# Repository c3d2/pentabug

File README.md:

pentabug
========

**If you experience difficulties with your bug, please check the [troubleshooting documentation](https://github.com/c3d2/pentabug/blob/master/troubleshooting.md).**

The pentabug is a small microcontroller soldering project. It's especially suited for young hackers and beginners of all ages. Assembly requires no prior soldering skills and can be accomplished - with a little help for the tricky parts - by children old enough to savely hold a soldering iron (thats about 7 years and up).

At various events, e.g. [Datenspuren 2012 and 2013](http://datenspuren.de "Datenspuren 2012 and 2013"), Chaos Communication Congress 2012-2015, and many more, several hundred kits have been successfully assembled with just a handfull of bugs needing 'special treatment' for e.g. a controller mounted the wrong way. Have a look at our [slides in german](/c3d2/pentabug/raw/master/doc/201210_slides_datenspuren.pdf "slides form the Datenspuren 2012 talk") from the accompanying [presentation](http://www.datenspuren.de/2012/fahrplan/events/5074.de.html "pentabug talk announcement") or watch [this video](http://www.youtube.com/watch?v=HTBhXqNR6LY "Dresdner Piratencast Folge 14 - Datenspuren") of Frank and his sons beeing interviewed at our workshop table or the [NDR report](https://www.ndr.de/fernsehen/sendungen/hamburg_journal/Kleine-Hacker-am-Werk,hamj45298.html) covering the 32c3 Junghackertag.

A complete walktrough of the assembly process is given in ["Pentabug - The Movie"](http://www.c3d2.de/news/video-pentabug-bauen.html "Pentabug - The Movie"), courtesy of [C3D2 - Chaos Computer Club Dresden](http://c3d2.de "C3D2 - Chaos Computer Club Dresden"). It would be amazing if Scott Manley could do an english version ;-). I would even visit SF to make that happen. 

Img. 1: A completely assembled V2 PCB with extension boards.

Img. 2: A slightly advanced (but early) prototype version of the bug with a single layer pcb.

Img. 3: The top layer view of the Version 1.0 production board (two layer pcb).

Img. 4: Version 2.1 schematics ([high resolution image](https://github.com/c3d2/pentabug/raw/master/img/schematics_v2_1.png "high resolution image of schematics")).

[Bill of Materials for Version 1.0](https://github.com/c3d2/pentabug/blob/master/bom.md "bill of materials") - CAVE: This is outdated for the V2.0 and V2.1 versions.

Programming
===========

A quite comprehensive documentation in German for setting up the development toolchain is available at [RHOIO's Blog](https://rhoio.wordpress.com/2014/02/06/den-pentabug-programmieren/).

AVR GCC Toolchain
------------------

 * install binutils-avr, gcc-avr, avr-libc, avrdude
 <pre><code>sudo apt-get install binutils-avr gcc-avr avr-libc avrdude</code></pre>

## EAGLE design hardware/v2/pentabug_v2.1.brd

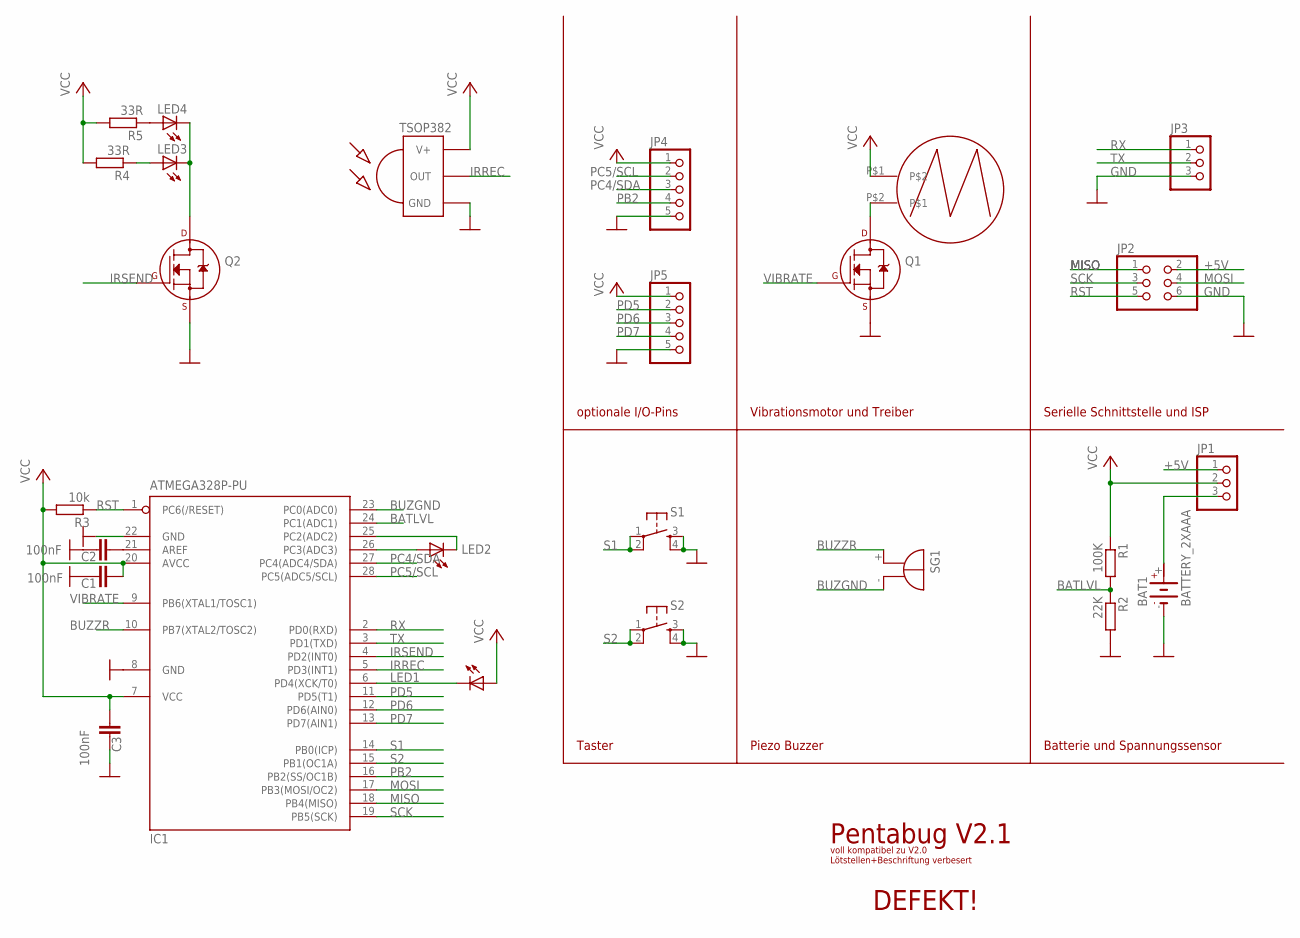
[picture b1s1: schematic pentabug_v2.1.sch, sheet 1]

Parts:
BAT1: BATTERY_2XAAA; BATTERY_2XAAA_SMALLPINS
C1, C2, C3: 100nF; C025-024X044
IC1: ATMEGA328P-PU; DIL28-3
IR: TSOP382
JP1, JP3: PINHD-1X3; 1X03
JP2: PINHD-2X3; 2X03
JP4, JP5: PINHD-1X5; 1X05
LED1, LED2: LED5MM
LED3, LED4: LED3MM
Q1, Q2: 2N7000; TO92-
R1: 100K; 0207/10
R2: 22K; 0207/10
R3: 10k; 0207/10
R4, R5: 33R; 0207/10
S1, S2: TAC_SWITCHPTH; TACTILE-PTH
SG1: MULTIBUZZRTDKBUZZR; BUZZRTDK
U$1: VIBRAMOTOR; LA4-432

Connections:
+5V: JP1.1, JP2.2
BAT: BAT1.+, JP1.3
BATLVL: IC1.24 (PC1(ADC1)), R1.2, R2.1
BUZGND: IC1.23 (PC0(ADC0)), SG1.-
BUZZR: IC1.10 (PB7(XTAL2/TOSC2)), SG1.+
GND: BAT1.-, C1.1, C2.1, C3.1, IC1.8 (GND), IC1.22 (GND), IR.GND, JP2.6, JP3.3, JP4.5, JP5.5, Q1.1 (S), Q2.1 (S), R2.2, S1.3, S1.4, S2.3, S2.4
IRREC: IC1.5 (PD3(INT1)), IR.OUT
IRSEND: IC1.4 (PD2(INT0)), Q2.2 (G)
MISO: IC1.18 (PB4(MISO)), JP2.1
MOSI: IC1.17 (PB3(MOSI/OC2)), JP2.4
unnamed: IC1.26 (PC3(ADC3)), LED2.A
unnamed: IC1.25 (PC2(ADC2)), LED2.K (C)
unnamed: LED4.A, R5.1
unnamed: Q1.3 (D), U$1.P$2
unnamed: LED3.A, R4.1
unnamed: LED3.K (C), LED4.K (C), Q2.3 (D)
unnamed: IC1.6 (PD4(XCK/T0)), LED1.K (C)
unnamed: C2.2, IC1.21 (AREF)
PB2: IC1.16 (PB2(SS/OC1B)), JP4.4
PC4/SDA: IC1.27 (PC4(ADC4/SDA)), JP4.3
PC5/SCL: IC1.28 (PC5(ADC5/SCL)), JP4.2
PD5: IC1.11 (PD5(T1)), JP5.2
PD6: IC1.12 (PD6(AIN0)), JP5.3
PD7: IC1.13 (PD7(AIN1)), JP5.4
RST: IC1.1 (PC6(/RESET)), JP2.5, R3.1
RX: IC1.2 (PD0(RXD)), JP3.1
S1: IC1.14 (PB0(ICP)), S1.1, S1.2
S2: IC1.15 (PB1(OC1A)), S2.1, S2.2
SCK: IC1.19 (PB5(SCK)), JP2.3
TX: IC1.3 (PD1(TXD)), JP3.2
VCC: C1.2, C3.2, IC1.7 (VCC), IC1.20 (AVCC), IR.VCC (V+), JP1.2, JP4.1, JP5.1, LED1.A, R1.1, R3.2, R4.2, R5.2, U$1.P$1
VIBRATE: IC1.9 (PB6(XTAL1/TOSC1)), Q1.2 (G)

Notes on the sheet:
Serielle Schnittstelle und ISP
DEFEKT!
Vibrationsmotor und Treiber
optionale I/O-Pins
Taster
Piezo Buzzer
Batterie und Spannungssensor
Pentabug V2.1
voll kompatibel zu V2.0 Lötstellen+Beschriftung verbesert

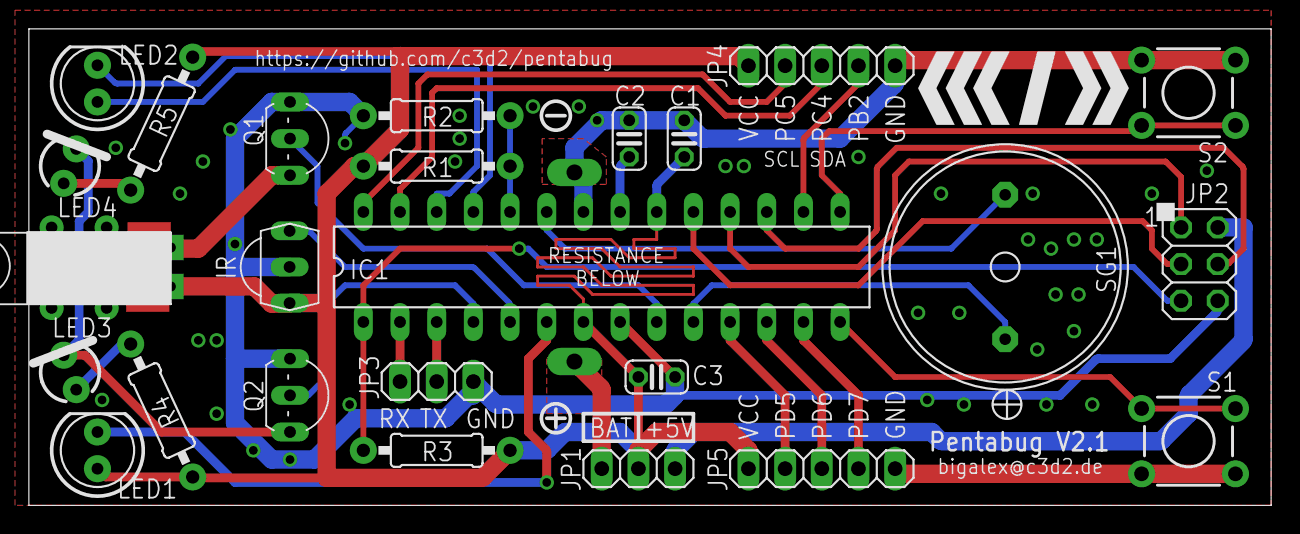
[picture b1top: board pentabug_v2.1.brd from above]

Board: 2 copper layers, 86.0 x 33.0 mm, 26 parts (1 on the bottom side), 32 nets.

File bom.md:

# Parts List

<table>
<tr><th>Bezeichnung	</th><th>Bauteil</th><th>Hinweis</th></tr>
<tr><td>n/a		</td><td>Leiterplatte V1.0		</td><td></td><tr>
<tr><td>IC1		</td><td>Mikrocontroller ATMEGA88PA	</td><td>Einbaulage beachten</td><tr>
<tr><td>R1		</td><td>Widerstand 100K		</td><td>braun-schwarz-schwarz-gelb-braun</td><tr>
<tr><td>R2		</td><td>Widerstand 22K			</td><td>rot-rot-scharz-rot-braun</td><tr>
<tr><td>R3		</td><td>Widerstand 10K			</td><td>braun-schwarz-schwarz-rot-braun</td><tr>
<tr><td>Q1		</td><td>Transistor 2N7000		</td><td>Einbaulage beachten</td><tr>
<tr><td>C1, C2, C3	</td><td>Keramikkondensator 100nF	</td><td></td><tr>
<tr><td>LED1, LED2	</td><td>LED rot			</td><td>Polarität beachten</td><tr>
<tr><td>SG1		</td><td>Piezo Buzzer			</td><td></td><tr>
<tr><td>JP1		</td><td>Stiftleiste 1x3		</td><td></td><tr>
<tr><td>JP2		</td><td>Stiftleiste 2x3		</td><td></td><tr>
<tr><td>S1, S2		</td><td>Taster				</td><td></td><tr>
<tr><td>M1		</td><td>Motor				</td><td></td><tr>
<tr><td>BAT1		</td><td>Batteriefach			</td><td>erst nach Test auf Platinenunterseite montieren</td><tr>
</table>


# cost calculation for 100 kits:

<pre><code>
name		description 	ben.Anzahl 	quelle/bestnr. 		einzelpreis(cent) 	summe(Euro)
---------	--------- 	----------- 	--------------  	----------------- 	--------------
IC1		ATMEGA88PA 	100 		mouser 			144 			144
BAT1		Batteriefach 	50 		hbc 			74 			~40
M1		motor(schwarz) 	100 		pollin 			125 			125
SG1		piezo buzzer	100 		mouser 			49			49
R1, R2, R3	widerst. 	300 		reichelt 		2.5 			7.50
Q1		2n7000 		100 		reichelt 		5 			5
C1, C2, C3	100nF 		300 		reichelt 		7 			21
JP1		head1x3 	100 		reichelt? 		7 			7
JP2		head2x3 	100 		reichelt? 		15 			15
LED1, LED2	ledSLH 56 	200 		reichelt 		7 			14
S1, S2		tacswitch	200		???			???			???
n/a		platine 	100 		mkpcb? 			150? 			~150
n/a		stahl.8mm 	25 		conrad 			50 			12.5
n/a		lötzinn 	1 		pollin 			795 			8
n/a		flyerA5 	100 		diekopie?  		3 			3
n/a		tüte 		100 		todo 			5 			5
n/a		glitzer 	100 		todo 			20 			20
n/a		glitter 	100 		todo 			20 			20
n/a		verbrauchsm     4  		dealer 			250 			10
n/a		aterial 	4 		dealer2 		250 			10
n/a		buzz variante   100 		reichelt 		10 			10
n/a		schmelzkleber 	1 		? 			1000 			10
n/a		sonstiges 	1 		dealer3 		115 			11.5
												summe:
											------------------------

										
------------------------------------------------------------------------------------------------

<code>										700
</pre>

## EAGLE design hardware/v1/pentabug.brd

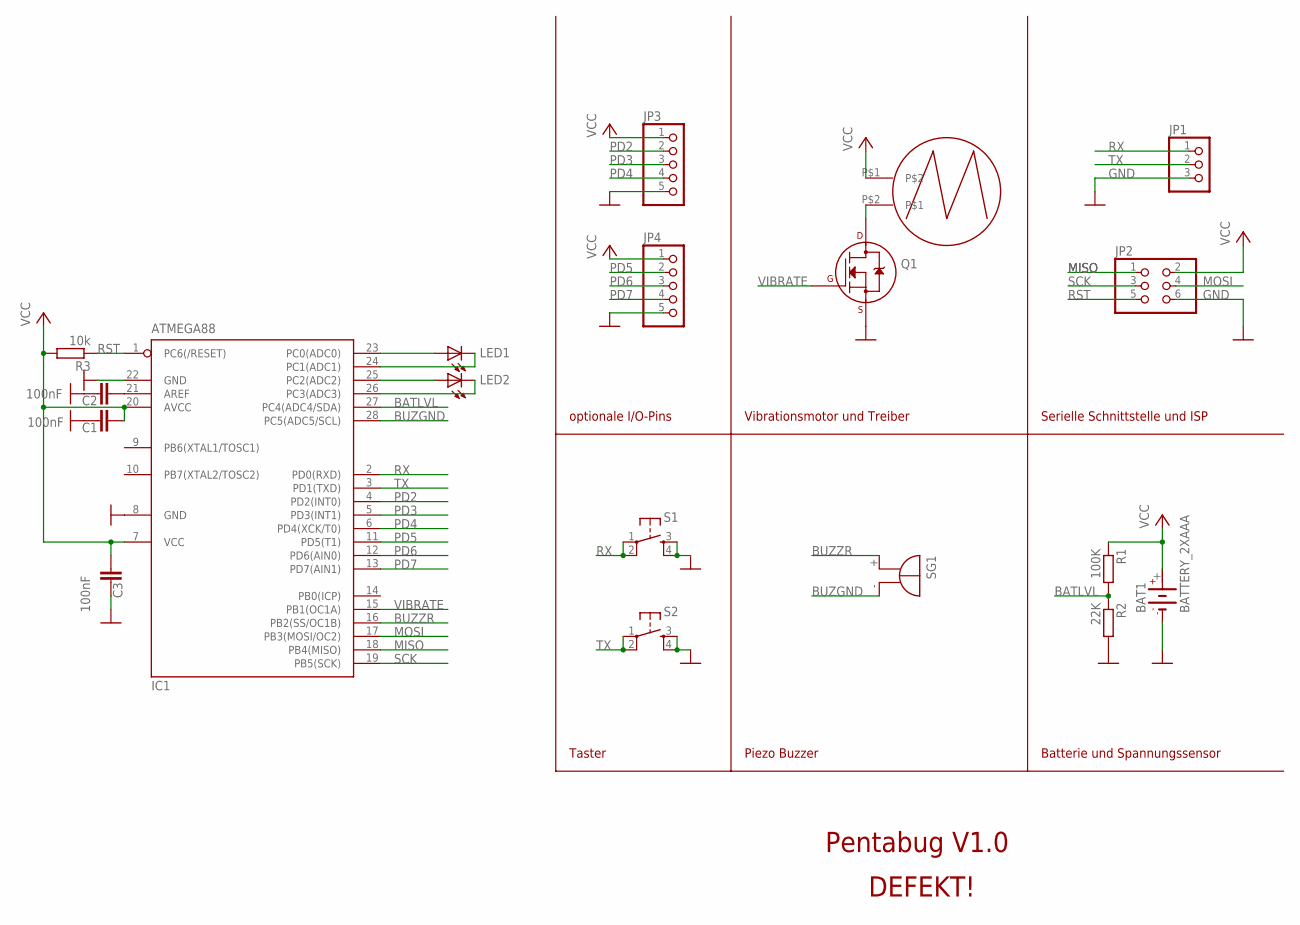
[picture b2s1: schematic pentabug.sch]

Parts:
BAT1: BATTERY_2XAAA
C1, C2, C3: 100nF; C025-024X044
IC1: ATMEGA88; DIL28-3
JP1: PINHD-1X3; 1X03
JP2: PINHD-2X3; 2X03
JP3, JP4: PINHD-1X5; 1X05
LED1, LED2: LED5MM
Q1: 2N7000_TO92; TO-92
R1: 100K; 0207/10
R2: 22K; 0207/10
R3: 10k; 0207/10
S1, S2: TAC_SWITCHPTH; TACTILE-PTH
SG1: MULTIBUZZRTDKBUZZR; BUZZRTDK
U$1: VIBRAMOTOR; LA4-432

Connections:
BATLVL: IC1.27 (PC4(ADC4/SDA)), R1.2, R2.1
BATTLVL: IC1.26 (PC3(ADC3)), LED2.K (C)
BUZGND: IC1.28 (PC5(ADC5/SCL)), SG1.-
BUZZR: IC1.16 (PB2(SS/OC1B)), SG1.+
GND: BAT1.-, C1.1, C2.1, C3.1, IC1.8 (GND), IC1.22 (GND), JP1.3, JP2.6, JP3.5, JP4.5, Q1.1 (S), R2.2, S1.3, S1.4, S2.3, S2.4
MISO: IC1.18 (PB4(MISO)), JP2.1
MOSI: IC1.17 (PB3(MOSI/OC2)), JP2.4
unnamed: IC1.23 (PC0(ADC0)), LED1.A
unnamed: IC1.25 (PC2(ADC2)), LED2.A
unnamed: Q1.3 (D), U$1.P$2
unnamed: IC1.24 (PC1(ADC1)), LED1.K (C)
unnamed: C2.2, IC1.21 (AREF)
PD2: IC1.4 (PD2(INT0)), JP3.2
PD3: IC1.5 (PD3(INT1)), JP3.3
PD4: IC1.6 (PD4(XCK/T0)), JP3.4
PD5: IC1.11 (PD5(T1)), JP4.2
PD6: IC1.12 (PD6(AIN0)), JP4.3
PD7: IC1.13 (PD7(AIN1)), JP4.4
RST: IC1.1 (PC6(/RESET)), JP2.5, R3.1
RX: IC1.2 (PD0(RXD)), JP1.1, S1.1, S1.2
SCK: IC1.19 (PB5(SCK)), JP2.3
TX: IC1.3 (PD1(TXD)), JP1.2, S2.1, S2.2
VCC: BAT1.+, C1.2, C3.2, IC1.7 (VCC), IC1.20 (AVCC), JP2.2, JP3.1, JP4.1, R1.1, R3.2, U$1.P$1
VIBRATE: IC1.15 (PB1(OC1A)), Q1.2 (G)

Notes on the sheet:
Serielle Schnittstelle und ISP
DEFEKT!
Vibrationsmotor und Treiber
optionale I/O-Pins
Taster
Piezo Buzzer
Batterie und Spannungssensor
Pentabug V1.0

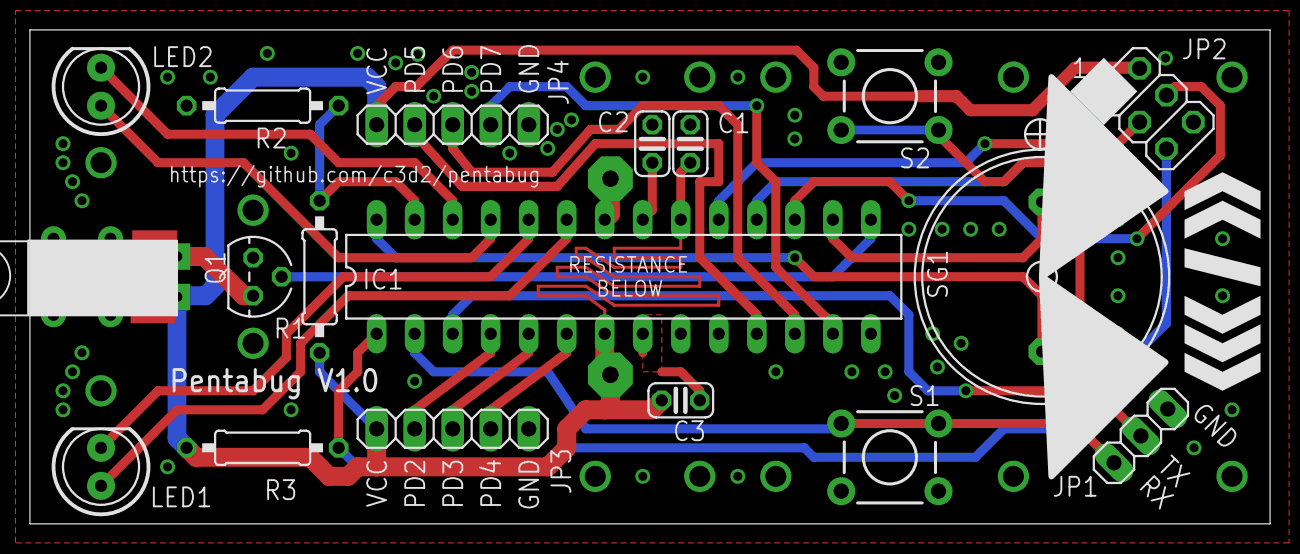
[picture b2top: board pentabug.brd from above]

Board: 2 copper layers, 82.9 x 33.0 mm, 19 parts (1 on the bottom side), 24 nets.

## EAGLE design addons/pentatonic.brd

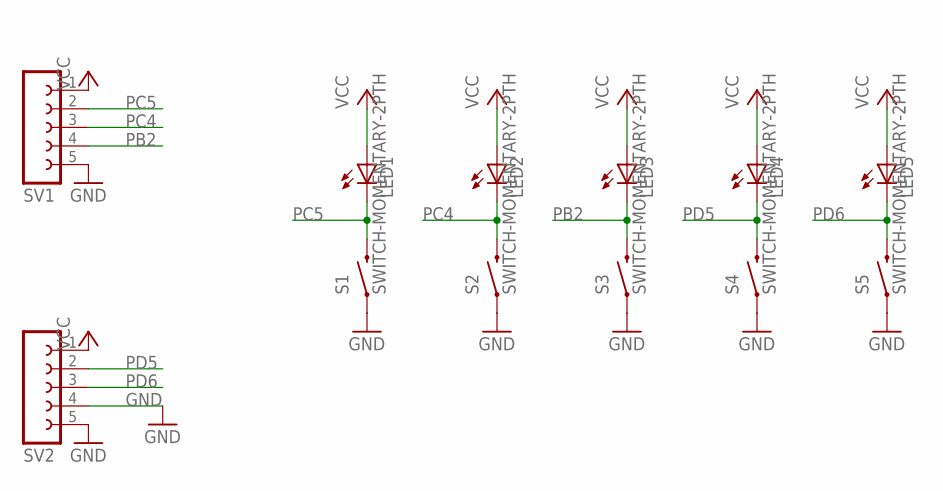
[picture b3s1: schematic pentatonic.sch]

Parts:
LED1, LED2, LED3, LED4, LED5: LED5MM
S1, S2, S3, S4, S5: SWITCH-MOMENTARY-2PTH; TACTILE-PTH
SV1, SV2: FE05-1

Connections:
GND: S1.1, S2.1, S3.1, S4.1, S5.1, SV1.5, SV2.4, SV2.5
PB2: LED3.K (C), S3.3 (2), SV1.4
PC4: LED2.K (C), S2.3 (2), SV1.3
PC5: LED1.K (C), S1.3 (2), SV1.2
PD5: LED4.K (C), S4.3 (2), SV2.2
PD6: LED5.K (C), S5.3 (2), SV2.3
VCC: LED1.A, LED2.A, LED3.A, LED4.A, LED5.A, SV1.1, SV2.1

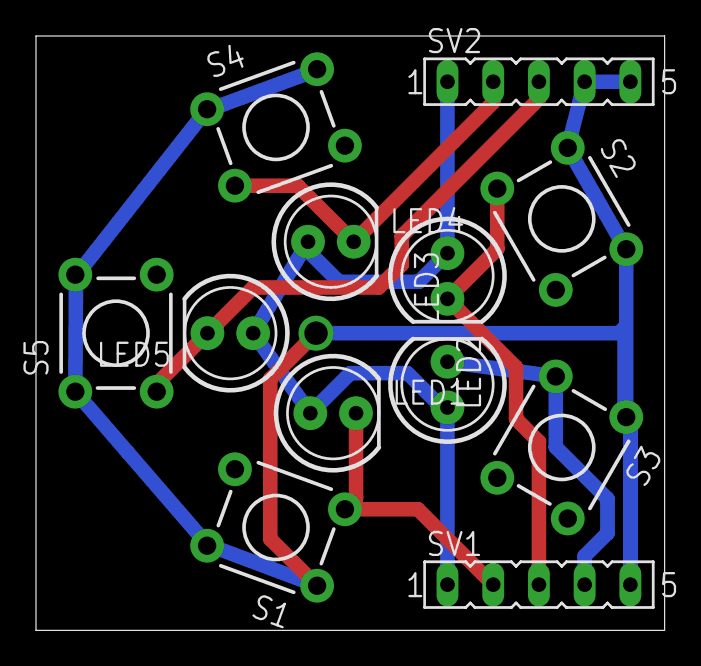
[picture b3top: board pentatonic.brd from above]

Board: 2 copper layers, 34.9 x 33.0 mm, 12 parts (0 on the bottom side), 7 nets.

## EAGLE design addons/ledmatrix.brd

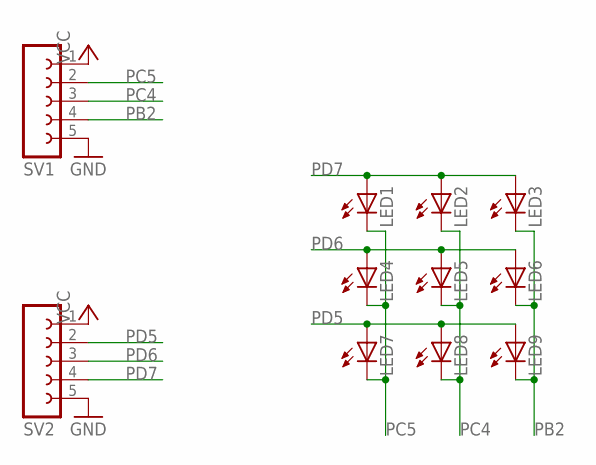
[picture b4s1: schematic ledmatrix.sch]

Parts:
LED1, LED2, LED3, LED4, LED5, LED6, LED7, LED8, LED9: LED5MM
SV1, SV2: FE05-1

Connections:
GND: SV1.5, SV2.5
PB2: LED3.K (C), LED6.K (C), LED9.K (C), SV1.4
PC4: LED2.K (C), LED5.K (C), LED8.K (C), SV1.3
PC5: LED1.K (C), LED4.K (C), LED7.K (C), SV1.2
PD5: LED7.A, LED8.A, LED9.A, SV2.2
PD6: LED4.A, LED5.A, LED6.A, SV2.3
PD7: LED1.A, LED2.A, LED3.A, SV2.4
VCC: SV1.1, SV2.1

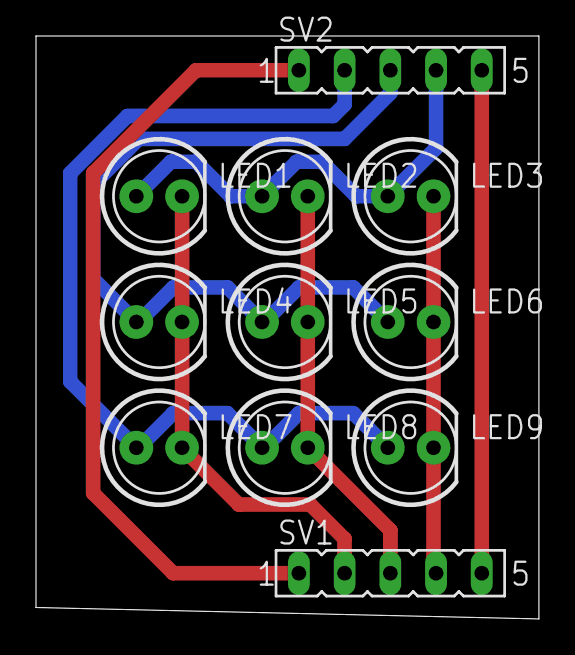
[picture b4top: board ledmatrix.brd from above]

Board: 2 copper layers, 27.9 x 32.4 mm, 11 parts (0 on the bottom side), 8 nets.

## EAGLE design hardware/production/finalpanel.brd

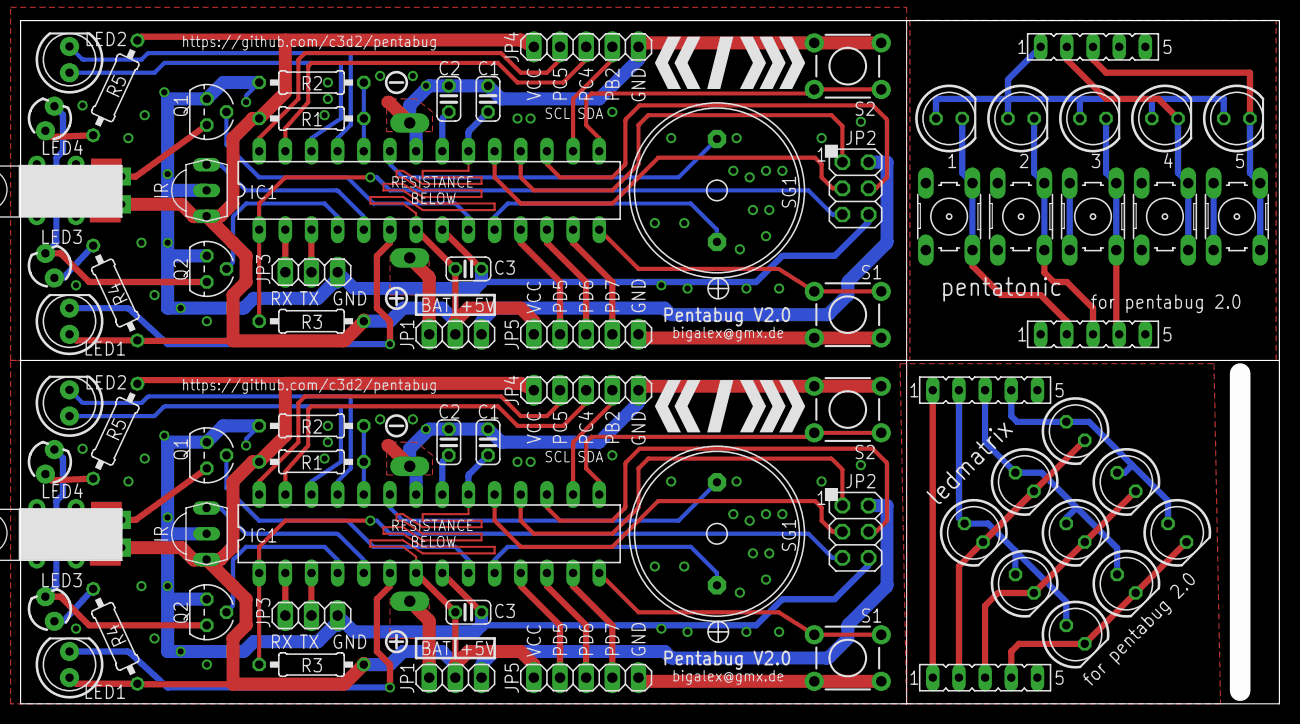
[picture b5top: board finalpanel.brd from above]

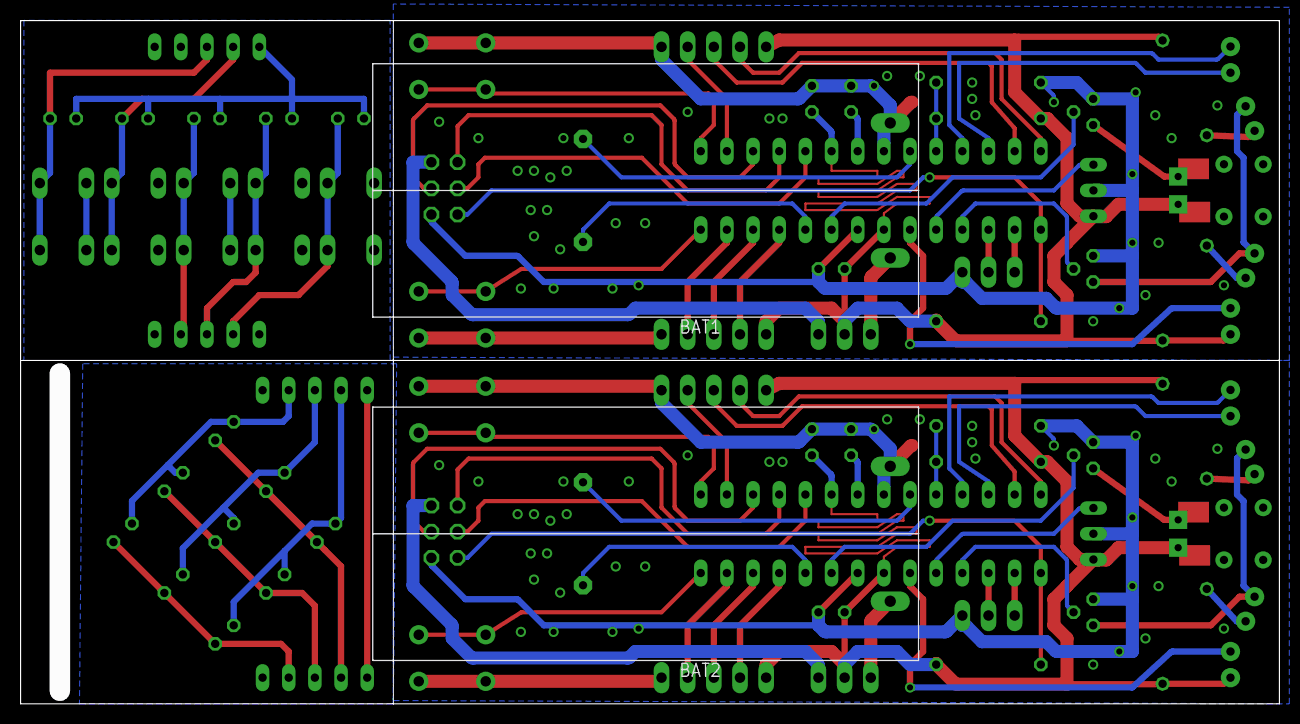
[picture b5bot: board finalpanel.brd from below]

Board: 2 copper layers, 120.2 x 64.3 mm, 75 parts (2 on the bottom side), 79 nets.

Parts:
BAT1, BAT2: BATTERY_2XAAA; BATTERY_2XAAA_SMALLPINS
C1, C2, C3, C4, C5, C6: 100nF; C025-024X044
IC1, IC2: ATMEGA88; DIL28-3
IR, IR1: TSOP382
JP1, JP3, JP6, JP10: 1X03
JP2, JP7: 2X03
JP4, JP5, JP8, JP9: 1X05
LED1, LED2, LED5, LED6, LED7, LED8, LED9, LED10, LED11, LED12, LED13, LED14, LED15, LED16, LED17, LED18, LED19, LED20: LED5MM
LED3, LED4, LED21, LED22: LED3MM
Q1, Q2, Q3, Q4: TO-92
R1, R7: 100K; 0207/10
R2, R8: 22K; 0207/10
R3, R6: 10k; 0207/10
R4, R5, R9, R10: 22R; 0207/10
S1, S2, S8, S9: TACTILE-PTH
S3, S4, S5, S6, S7: B3F-10XX
SG1, SG2: MULTIBUZZRTDKBUZZR; BUZZRTDK
SV4, SV5: FE05-1
SV__4, SV__5: FE05-1
U$1, U$2: VIBRAMOTOR; LA4-432

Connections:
+5V: JP1.1, JP2.2
+5V1: JP7.2, JP10.1
BAT: BAT1.+, JP1.3
BAT1: BAT2.+, JP10.3
BATLVL: IC1.24, R1.2, R2.1
BATLVL1: IC2.24, R7.2, R8.1
BUZGND: IC1.23, SG1.-
BUZGND1: IC2.23, SG2.-
BUZZR: IC1.10, SG1.+
BUZZR1: IC2.10, SG2.+
GND: BAT1.-, C1.1, C2.1, C3.1, IC1.8, IC1.22, IR.GND, JP2.6, JP3.3, JP4.5, JP5.5, Q1.1, Q2.1, R2.2, S1.3, S1.4, S2.3, S2.4
GND1: BAT2.-, C4.1, C5.1, C6.1, IC2.8, IC2.22, IR1.GND, JP6.3, JP7.6, JP8.5, JP9.5, Q3.1, Q4.1, R8.2, S8.3, S8.4, S9.3, S9.4
GND_L: SV__4.5, SV__5.5
GND_M: S3.3, S3.4, S4.3, S4.4, S5.3, S5.4, S6.3, S6.4, S7.3, S7.4, SV4.5, SV5.5
IRREC: IC1.5, IR.OUT
IRREC1: IC2.5, IR1.OUT
IRSEND: IC1.4, Q2.2
IRSEND1: IC2.4, Q4.2
MISO: IC1.18, JP2.1
MISO1: IC2.18, JP7.1
MOSI: IC1.17, JP2.4
MOSI1: IC2.17, JP7.4
unnamed: IC1.26, LED2.A
unnamed: IC1.25, LED2.K
unnamed: LED4.A, R5.1
unnamed: Q1.3, U$1.P$2
unnamed: C5.2, IC2.21
unnamed: LED3.A, R4.1
unnamed: LED3.K, LED4.K, Q2.3
unnamed: IC1.6, LED1.K
unnamed: Q3.3, U$2.P$2
unnamed: C2.2, IC1.21
unnamed: IC2.26, LED20.A
unnamed: IC2.25, LED20.K
unnamed: LED22.A, R10.1
unnamed: LED21.A, R9.1
unnamed: LED21.K, LED22.K, Q4.3
unnamed: IC2.6, LED19.K
PB1: IC2.16, JP9.4
PB2: IC1.16, JP4.4
PB2_L: LED12.K, LED15.K, LED18.K, SV__4.4
PB2_T: LED7.K, S5.1, S5.2, SV4.4
PC4_L: LED11.K, LED14.K, LED17.K, SV__4.3
PC4_T: LED6.K, S4.1, S4.2, SV4.3
PC5_L: LED10.K, LED13.K, LED16.K, SV__4.2
PC5_T: LED5.K, S3.1, S3.2, SV4.2
PD1: IC2.11, JP8.2
PD2: IC2.12, JP8.3
PD3: IC2.13, JP8.4
PD5: IC1.11, JP5.2
PD5_L: LED16.A, LED17.A, LED18.A, SV__5.2
PD5_T: LED8.K, S6.1, S6.2, SV5.2
PD6: IC1.12, JP5.3
PD6_L: LED13.A, LED14.A, LED15.A, SV__5.3
PD6_T: LED9.K, S7.1, S7.2, SV5.3
PD7: IC1.13, JP5.4
PD7_L: LED10.A, LED11.A, LED12.A, SV__5.4
RST: IC1.1, JP2.5, R3.1
RST1: IC2.1, JP7.5, R6.1
RX: IC1.2, JP3.1
RX1: IC2.2, JP6.1
S1: IC1.14, S1.1, S1.2
S2: IC1.15, S2.1, S2.2
S3: IC2.14, S9.1, S9.2
S4: IC2.15, S8.1, S8.2
SCK: IC1.19, JP2.3
SCK1: IC2.19, JP7.3
SCL: IC1.28, JP4.2
SCL1: IC2.28, JP9.2
SDA: IC1.27, JP4.3
SDA1: IC2.27, JP9.3
TX: IC1.3, JP3.2
TX1: IC2.3, JP6.2
VCC: C1.2, C3.2, IC1.7, IC1.20, IR.VCC, JP1.2, JP4.1, JP5.1, LED1.A, R1.1, R3.2, R4.2, R5.2, U$1.P$1
VCC1: C4.2, C6.2, IC2.7, IC2.20, IR1.VCC, JP8.1, JP9.1, JP10.2, LED19.A, R6.2, R7.1, R9.2, R10.2, U$2.P$1
VCC_L: SV__4.1, SV__5.1
VCC_M: LED5.A, LED6.A, LED7.A, LED8.A, LED9.A, SV5.1
VIBRATE: IC1.9, Q1.2
VIBRATE1: IC2.9, Q3.2

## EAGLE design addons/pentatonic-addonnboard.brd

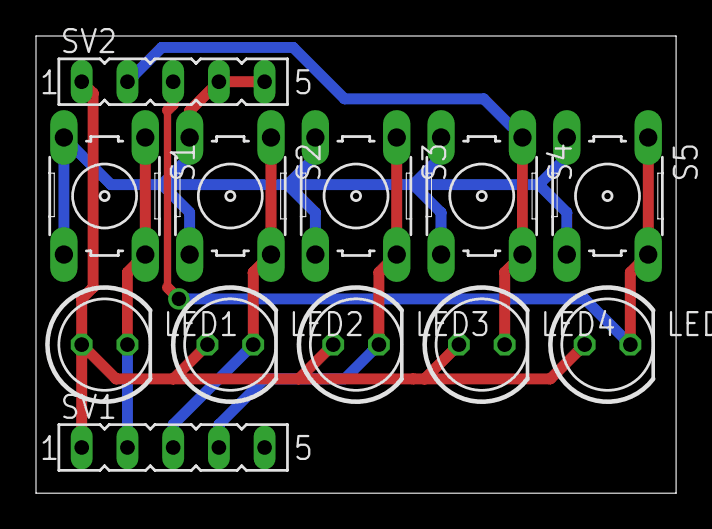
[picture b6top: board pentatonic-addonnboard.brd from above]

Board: 2 copper layers, 35.6 x 25.4 mm, 12 parts (0 on the bottom side), 7 nets.

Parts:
LED1, LED2, LED3, LED4, LED5: LED5MM
S1, S2, S3, S4, S5: B3F-10XX
SV1, SV2: FE05-1

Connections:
GND: S1.3, S1.4, S2.3, S2.4, S3.3, S3.4, S4.3, S4.4, S5.3, S5.4, SV1.5, SV2.4, SV2.5
PD2: LED1.K, S1.1, S1.2, SV1.2
PD3: LED2.K, S2.1, S2.2, SV1.3
PD4: LED3.K, S3.1, S3.2, SV1.4
PD5: LED4.K, S4.1, S4.2, SV2.2
PD6: LED5.K, S5.1, S5.2, SV2.3
VCC: LED1.A, LED2.A, LED3.A, LED4.A, LED5.A, SV1.1, SV2.1

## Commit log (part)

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2012-06-14 genesis, reusing pentalight
2012-07-03 initialer neuanfang board
2012-07-03 changed minimal stuff
2012-07-03 buzzer, motor, transistor added
2012-07-16 initial firmware... narf enabled
2012-07-16 bom initialized...
    still double buzzer...
2012-07-17 Buzzr connected to OC1B, motr driven against Vcc instead gnd
2012-07-18 testpwmcode
2012-07-18 reread datasheet.. this time awake
2012-07-24 adder real used mötör in special lib
2012-07-24 weiß nich mehr... motor pwm stuff
2012-07-24 Completed with no bugs...
2012-07-25 added timer0 isr and init
2012-07-26 did stuff
2012-07-26 call init_sampletimer
2012-07-26 nice accord
2012-07-30 added battery holder, bord layout changed to reflect later constellation of components
2012-07-30 centered motor package, switched motor pins for convienence
2012-07-30 some routing, buzzer footprint still wrong
2012-07-30 pulled minor changes in battery holder
2012-08-03 some more routing, added new buzzr footprint
2012-08-03 some routing
2012-08-05 changed make flash for serial bootlader to make serflash, changed make flash to support usbtiny isp programmer, set fuses to correct values (default, no brownout, but internal to 8 MHz insted of 1/8 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
2012-08-05 commit for sync
2012-08-05 some sound synthesis
2012-08-05 base frequency of pwm lowered
2012-08-05 really ignore ignored worsd
2012-08-05 polyphonie
2012-08-06 stand alone synth server
2012-08-06 different waveforms
2012-08-06 prepare playback if's
2012-08-06 make it quieter
2012-08-06 noise
2012-08-06 change test values
2012-08-06 added flash README
2012-08-06 fixmd
2012-08-06 all sample and legacy code thrown out of main
2012-08-06 markdowned bom
2012-08-06 markdown for real
2012-08-06 frequency table
2012-08-06 wrap freq lookup index
2012-08-06 some little melody
2012-08-06 reshuffle instrument
2012-08-07 removed USART test from ISR
2012-08-08 tune file reader (not working/done yet)
2012-08-08 parser done
2012-08-08 slow donw, put stuff into header
2012-08-08 good night
2012-08-08 allow symbles
2012-08-08 better tune, maybe
2012-08-08 comment song
2012-08-09 print out tune size
2012-08-09 improve instruments
2012-08-09 implement export_tune
2012-08-11 new tune
2012-08-11 Enabling timer 2 for LED testing
2012-08-11 Some code for measuring brightness, but not working yet
2012-08-12 Added just an icon.
2012-08-12 Lots of routing done, GND from Buzzer connected to ADC6 for measurement
2012-08-13 cleaned up and draw power lines
2012-08-13 made editable with eagle freeware!!
2012-08-13 inbetween
2012-08-13 sent patterns and freq_table to programspace to fix #1
2012-08-13 implemented timeslot queue to fix #2 but sound is still a bit strange
2012-08-13 final 0.1
2012-08-14 some synth --- sync
2012-08-14 8bitalized synth output stage 1
2012-08-14 sorry 2bt... need to play the 8bit way
2012-08-17 stil not satisfied with routing for 1 layer board
2012-08-19 routing finished
2012-08-21 modified to use biggr buzzr - routing not adapted yet!
2012-08-22 added federstahlstangen
2012-08-22 motor obergrenze genommen
2012-08-22 added bastelmaterial, glitzer glitter
2012-08-26 major routing improvents, placement und info prints
2012-08-27 minor fix
2012-08-27 bad bug fixed: removed cutout for vibra motor
2012-08-27 rolled back unwanted changes (testcode) to prevoius version in main.c
2012-08-28 fixed bad bad evil vias connecting Vcc and GND
2012-08-28 better connection for AVcc block capacitor, Moar vias FTW!
2012-08-29 moved vias away from print for LED2
2012-08-31 added pics (or it didn't happen)
2012-08-31 description for images
2012-09-02 spaces for linewrap in readme
2012-09-02 moved synth.c and usart.c to lib dir
2012-09-02 some schematics beautification
2012-09-02 Moved libraries to lib directory, added hardware abstraction lib
2012-09-02 minor typo in README
2012-09-02 next try at typo in readme
2012-09-02 consolidated build
2012-09-06 ggrcntrbug FTW!
2012-09-12 error corrected
2012-09-19 temporary sync
2012-09-19 link to BOM
2012-09-19 fixed table head
2012-09-19 fixed Makefile
2012-09-19 added aufbauflyer
2012-09-19 improved instruction flyer
2012-09-20 corrected font
2012-09-20 some more..
2012-09-20 tune for printer margin
2012-09-20 orthografische verbesserung
2012-09-20 test firmware added
2012-09-20 prepared some code for different modes
2012-09-21 adde automatedd batch programming
2012-09-24 start multimode testfw
2012-09-25 mhhh
2012-09-25 dangerous commets removed from autobaudratecalc
2012-09-25 not working yet
2012-09-27 working test firmware (yes, setting the pullups is a good idea)
2012-10-01 compact makefile
2012-10-01 small fix to make output
2012-10-01 increased BAUD_TOL from 2 to 4 to suppress warning
2012-10-01 code beautify
2012-10-01 backward compatibility for delay.h
2012-10-01 some cleanup
2012-10-01 removed backward compatibility for delay.h
2012-10-01 added Makefile for actually working beatifull Makefile
2012-10-01 fizzbug
2012-10-01 switch_l and switch_r in bughal work now
2012-10-01 demo for direct switch testing, led and motor control
2012-10-03 added make flsmart for use with mySmartUSB light ISP
2012-10-03 some sound with music notes and mode switching
2012-10-03 Mode0 is now ggrbug mode
2012-10-03 mode2 for funny movez
2012-10-05 initial schall test
2012-10-05 sync
2012-10-05 now detecting sound
2012-10-05 better sond measurment, tolerant to static voltage on piezo
2012-10-05 ADC free running
2012-10-05 rattling and beeping when detecting sound
2012-10-05 enable/disable sound and motot by switch in sound detection mode
2012-10-06 a bit code beautification
2012-10-07 usart: USART0_puts()
2012-10-07 main: beat replicat0r
2012-10-07 more coments and fixed a bug in crazymoves-mode
2012-10-08 measuring works but in dark light the slope is very flat
2012-10-08 measuring with adcbut 10ms is to slow for bright light and to fast for low light
2012-10-08 just measuring fotovoltage witch adc works (with vcc as ref)
2012-10-08 lighttest integratet to normal operation modes
2012-10-09 debug branch for synth rebuild
2012-10-09 rm freq_table.h
2012-10-09 proper prototype
2012-10-09 swap instead of pwm
2012-10-09 make it faster (:
2012-10-10 some more awesomeness
2012-10-10 added synth to mode1, major cleanup
2012-10-10 button code madness
2012-10-10 fixed bug
2012-10-10 prepared powerdown mode. implement switch combo, blink feedback and signal tone for powerdown interaction
2012-10-11 pwdown still needs isr to wakeup.
    put untested pdown code. please add pinchangeirq
    for either button
2012-10-11 Add compile stuff to gitignore
2012-10-11 Modularize modes to apps
2012-10-11 Make it compile again
2012-10-11 Deactivate modeswitch_poll() if power down in progress
2012-10-11 Revert "Move synth code from lib to app"
    This reverts commit 5dd5bdacaa6fcc6caa0e6b9ca2a81361f76a56e4.
2012-10-11 some stuff
2012-10-11 Revert "Revert "Move synth code from lib to app""
    This reverts commit d48a6d67d7a0cf14036afc941ecd6f05537cccd6.
2012-10-11 Fix the freqqing synth table
2012-10-11 coz shorter is always better
2012-10-11 turn off the motor before power down
2012-10-11 Add very simple cockroach
2012-10-11 cockroach: Remove code for second led
2012-10-12 cockroach: Some random behaviour
2012-10-12 crazy synth: Fix typo
2012-10-12 Disable crazy mode
2012-10-12 url with initX section voodo added
2012-10-13 Add timer abstraction
2012-10-13 sound detect: deinitialize sound detection mode
2012-10-13 sound effect
2012-10-18 Added slides, links and infos about pentabug at Datenspuren 2012
2012-10-18 added editor backup files and eagle backup files to .gitignore
2012-12-20 fixed some typos, scaledown for 4up version
2012-12-26 Images for 29c3
2013-01-03 added slides from 29c3 lightning talk
2013-03-13 Absolute URL
    Mit absoluter URL werden auch die Bilder angezeigt. ;)
2013-07-06 bug v2 genesis (now with IR!)
2013-07-07 some beautifications
2013-07-07 anpassen an neues board
2013-07-07 brauchen wir nicht/doppelt
2013-07-08 delte some older files
2013-07-08 Addons are already integrated as own sheet in pentabug v2
2013-07-08 correcting minor glitch (unrouted) in ledmatrix (thanks a lot to the guys from makepcb)
2013-07-08 production files
2013-07-14 moar kalkulation
2013-07-14 einkaufslisten
2013-07-25 bestellungen nicht auf github
2013-08-08 druckbares bestückungsding
2013-08-15 Adjust test code to new hardware
2013-08-15 Test firmware can test all parts
2013-08-15 Better comments
2013-08-15 Add readme to test firmware
2013-08-26 Make the non-working skeleton work
2013-08-26 Add interrupts, music and much more stuff
2013-08-26 Less awkward ir signal generation
2013-08-26 Add melody support and hal stubs
2013-08-26 Turn off IR, use HAL in blink and implement some HAL
2013-08-28 New fancy test firmware
2013-08-29 Add and use wait_ms(); fix some timings
2013-08-29 Add unused headers and unnecessary test_stop_app() calls
2013-08-29 Add motor test application
2013-08-29 Do not attempt to drive the motor with the pullup ...
2013-08-29 fw test: Flash in photon mode and improved documentation
2013-08-29 Improved music code
2013-08-29 Use melody code for music app
2013-08-30 fixes issue #6, correct values for r4 and r5
2013-08-30 Add buzzer functions and some documentation in the code
2013-08-30 Add documentation to music.c and minor fix to MLDY_PAUSE
2013-08-30 Rename music app
2013-08-30 Add notes to buzzer functions
2013-08-30 Add initial pentatonic support
2013-08-30 Add buttons to pentatonic API
2013-08-30 Save data memory
2013-08-30 Revert "Save data memory"
    This reverts commit 589275a3ba60d22ac40dd321cf04ef8e06009381.
2013-08-30 Add IR to HAL
2013-08-31 Add attempt to implement RC-5 sending
2013-08-31 Attempt to port light detection code, not working yet
2013-08-31 Extend TODOs
2013-09-03 Working light measurement
2013-09-03 Add buggy behaviour
2013-09-03 Be more noisy
2013-09-03 Remove dead code
2013-09-03 Add motor stuff to blinker
2013-09-03 improve music
2013-09-03 tune app switch sound
2013-09-03 implement five key piano
2013-09-03 Add geiger app
2013-09-04 longer notes
2013-09-04 clear osc on note-off-event
2013-09-04 Move button handling to own timer for better performance
2013-09-04 move const data to progmem
2013-09-05 Add octave switching to pentatonic app
2013-09-05 complete the tune
2013-09-05 make it faster and higher
2013-09-05 apparently int is larger than uint8_t :P
2013-09-05 Toggle LEDs around playing mario theme (instead of on/off)
2013-09-05 change blink
2013-09-05 comment
2013-09-05 mario theme: Make baseline flash
2013-09-05 Remove old warning
2013-09-05 Add missing header to timer
2013-09-05 introduced timer divider
2013-09-05 Add german documentation and matrix code
2013-09-05 Make blinker simpler
2013-09-05 entwurf einer irempfargstatemachine skizziert....
    sry mehr ging heute einfach nicht mehr.... wir sollten um schnell was zu
    haben mal eine solche kacke runtercoden, und das senden dann
    dementsprechend machen.... ich schlage vor das eine msg immer 2 byte
    lang ist ... sowas wie adresse, keycode ... oder eben einfach eine
    temperatur oder wtf.... jedenfalls feste länge....
2013-09-05 Add IR stuff to buggy app
2013-09-05 More reaction on light
2013-09-06 Better buggy behaviour
2013-09-07 Add ledmatrix support
2013-09-08 matrix: Add brightness
2013-09-20 correct labels for ledmatrix nets fixes #8
2013-09-20 marked cathode for IR led3 and led4, fixes #9
2013-09-21 Add wuerfel to Makefile
2013-09-21 Remove some compiler warnings
2013-12-16 New simpler test firmware
2013-12-20 added DS2012 logo
2014-01-03 started with v2.1 - easy-solder resistors FTW
2014-01-03 some improvent on placement of print and mounting holes for motor
2014-01-08 moar easy soldering
2014-01-08 some instruction flyers and mekadile changes
2014-01-10 Padawan Doku first commit
2014-01-10 Bauteilbeschreibungen
2014-08-28 v2.1 production files, updated docs, some cleanup
2014-08-28 new order of components
2014-09-01 aufteilung sammelbest.
2014-09-13 Adjust thresholds
2014-10-23 doc/de/teil_1:episode_2.md: typo fixed
2014-11-24 add chat app
    two (or more) pentabugs can have a chat with each other.
    It is made shure via IR, that only one bug talks at a time.
    4 different voices can be choosen with the two buttons, as well as
    random voice select
2014-12-08 ordering parts for 31c3 and some stuff for future projects
2014-12-20 packing list added
2015-03-11 Add install guide
2015-03-11 Add examples and tasks
2015-03-11 schematics 2.1 as image
2015-03-11 typo fixed

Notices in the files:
parts and their libraries:
SparkFun: Licensing: CC v3.0 Share-Alike You are welcome to use this library for commercial purposes.
